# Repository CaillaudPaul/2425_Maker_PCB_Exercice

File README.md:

# 2425_Maker_PCB_Exercice
Creation of a PCB to control a DC motor

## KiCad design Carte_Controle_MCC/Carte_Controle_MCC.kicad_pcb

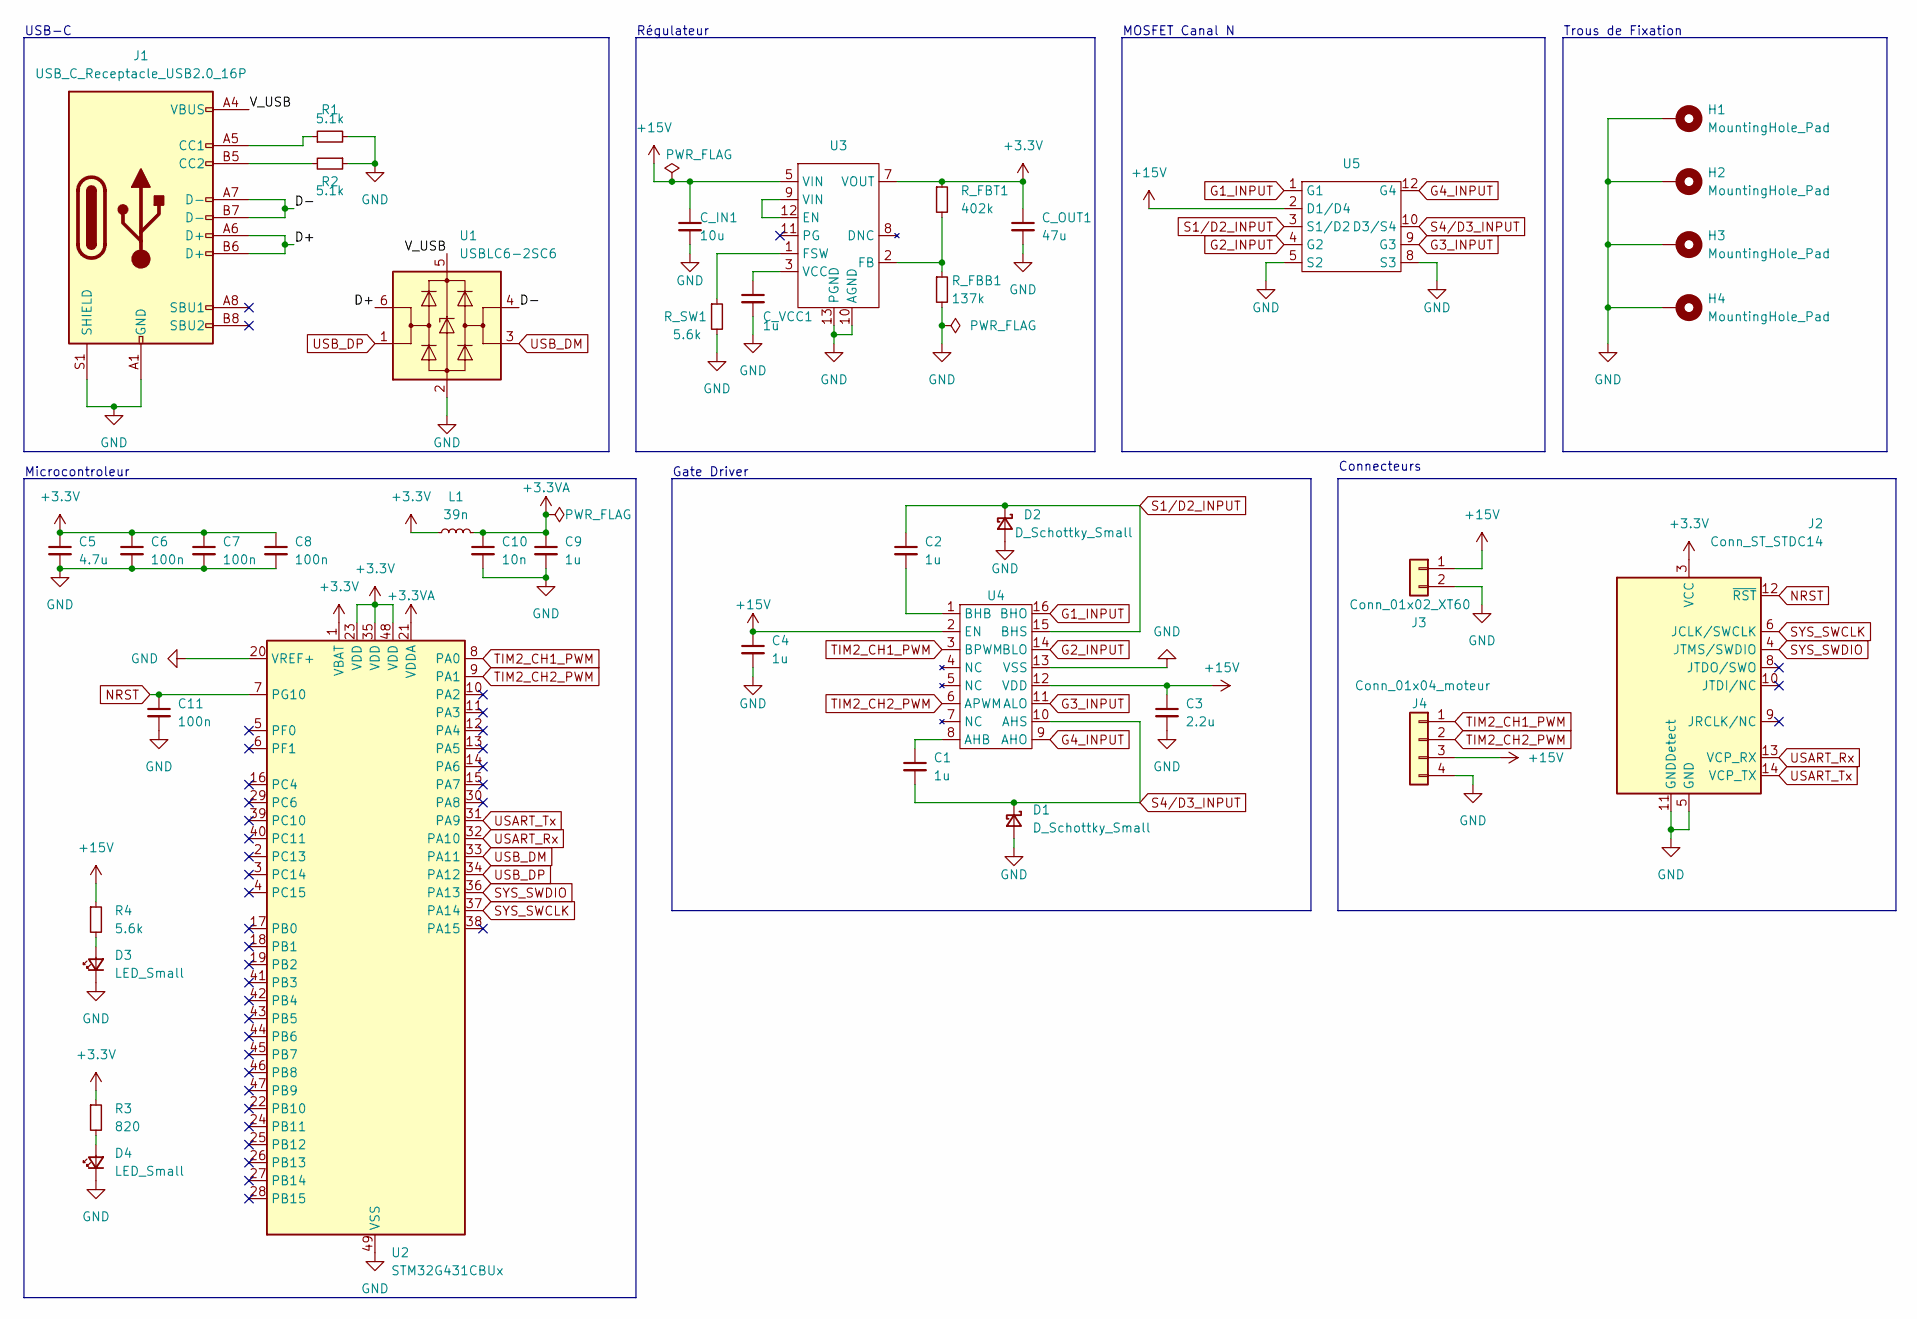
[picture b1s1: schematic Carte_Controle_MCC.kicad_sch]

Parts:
C1, C2, C4, C9: 1u; C_0201_0603Metric_Pad0.64x0.40mm_HandSolder
C3: 2.2u; C_0201_0603Metric_Pad0.64x0.40mm_HandSolder
C5: 4.7u; C_0201_0603Metric_Pad0.64x0.40mm_HandSolder
C6, C7, C8, C11: 100n; C_0201_0603Metric_Pad0.64x0.40mm_HandSolder
C10: 10n; C_0201_0603Metric_Pad0.64x0.40mm_HandSolder
C_IN1: 10u; C_0201_0603Metric_Pad0.64x0.40mm_HandSolder
C_OUT1: 47u; C_0201_0603Metric_Pad0.64x0.40mm_HandSolder
C_VCC1: 1u; C_0201_0603Metric_Pad0.64x0.40mm_HandSolder
D1, D2: D_Schottky_Small; D_0603_1608Metric_Pad1.05x0.95mm_HandSolder
D3, D4: LED_Small; LED_0603_1608Metric_Pad1.05x0.95mm_HandSolder
H1, H2, H3, H4: MountingHole_Pad; MountingHole_3.2mm_M3_DIN965_Pad
J1: USB_C_Receptacle_USB2.0_16P; USB_C_Receptacle_G-Switch_GT-USB-7010ASV
J2: Conn_ST_STDC14; PinHeader_2x07_P1.27mm_Vertical_SMD
J3: Conn_01x02_XT60; AMASS_XT60-M_1x02_P7.20mm_Vertical
J4: Conn_01x04_moteur; JST_EH_B4B-EH-A_1x04_P2.50mm_Vertical
L1: 39n; L_0805_2012Metric_Pad1.05x1.20mm_HandSolder
R1, R2: 5.1k; R_0603_1608Metric_Pad0.98x0.95mm_HandSolder
R3: 820; R_0603_1608Metric_Pad0.98x0.95mm_HandSolder
R4: 5.6k; R_0603_1608Metric_Pad0.98x0.95mm_HandSolder
R_FBB1: 137k; R_0603_1608Metric_Pad0.98x0.95mm_HandSolder
R_FBT1: 402k; R_0603_1608Metric_Pad0.98x0.95mm_HandSolder
R_SW1: 5.6k; R_0603_1608Metric_Pad0.98x0.95mm_HandSolder
U1: USBLC6-2SC6; SOT-23-6
U2: STM32G431CBUx; QFN-48-1EP_7x7mm_P0.5mm_EP5.6x5.6mm
U3: wurth_171013801
U4: Gate_Driver_MIC4606-2YTS-TR
U5: Mosfet_FDMQ86530L

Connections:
+3.3V: C5.1, C6.1, C7.1, C8.1, C_OUT1.1, J2.3 (VCC), L1.1, R3.1, R_FBT1.1, U2.1 (VBAT), U2.23 (VDD), U2.35 (VDD), U2.48 (VDD), U3.6 (VOUT), U3.7 (VOUT)
+3.3VA: C9.1, C10.1, L1.2, U2.21 (VDDA)
+15V: C3.1, C4.1, C_IN1.1, J3.1, J4.3, R4.1, U3.4 (VIN), U3.5 (VIN), U4.2 (EN), U4.12 (VDD), U5.2 (D1/D4), U5.11 (D1/D4), U5.13 (D1/D4)
/D+: J1.A6 (D+), J1.B6 (D+), U1.6 (I/O1)
/D-: J1.A7 (D-), J1.B7 (D-), U1.4 (I/O2)
/V_USB: J1.A4 (VBUS), J1.A9 (VBUS), J1.B4 (VBUS), J1.B9 (VBUS), U1.5 (VBUS)
G1_INPUT: U4.16 (BHO), U5.1 (G1)
G2_INPUT: U4.14 (BLO), U5.4 (G2)
G3_INPUT: U4.11 (ALO), U5.9 (G3)
G4_INPUT: U4.9 (AHO), U5.12 (G4)
GND: C3.2, C4.2, C5.2, C6.2, C7.2, C8.2, C9.2, C10.2, C11.2, C_IN1.2, C_OUT1.2, C_VCC1.2, D1.2 (A), D2.2 (A), D3.1 (K), D4.1 (K), H1.1, H2.1, H3.1, H4.1, J1.A1 (GND), J1.A12 (GND), J1.B1 (GND), J1.B12 (GND), J1.S1 (SHIELD), J2.5 (GND), J2.7 (GND), J2.11 (GNDDetect), J3.2, J4.4, R1.2, R2.1, R_FBB1.2, R_SW1.2, U1.2 (GND), U2.20 (VREF+), U2.49 (VSS), U3.10 (AGND), U3.13 (PGND), U4.13 (VSS), U5.5 (S2), U5.6 (S2), U5.7 (S3), U5.8 (S3)
NRST: C11.1, J2.12 (~RST), U2.7 (PG10)
unnamed: D3.2 (A), R4.2
unnamed: D4.2 (A), R3.2
unnamed: J1.A5 (CC1), R1.1
unnamed: J1.B5 (CC2), R2.2
unnamed: U3.9 (VIN), U3.12 (EN)
unnamed: R_FBB1.1, R_FBT1.2, U3.2 (FB)
unnamed: R_SW1.1, U3.1 (FSW)
unnamed: C_VCC1.1, U3.3 (VCC)
unnamed: C1.1, U4.8 (AHB)
unnamed: C2.2, U4.1 (BHB)
S1/D2_INPUT: C2.1, D2.1 (K), U4.15 (BHS), U5.3 (S1/D2), U5.14 (S1/D2)
S4/D3_INPUT: C1.2, D1.1 (K), U4.10 (AHS), U5.10 (D3/S4), U5.15 (D3/S4)
SYS_SWCLK: J2.6 (JCLK/SWCLK), U2.37 (PA14)
SYS_SWDIO: J2.4 (JTMS/SWDIO), U2.36 (PA13)
TIM2_CH1_PWM: J4.1, U2.8 (PA0), U4.3 (BPWM)
TIM2_CH2_PWM: J4.2, U2.9 (PA1), U4.6 (APWM)
USART_Rx: J2.13 (VCP_RX), U2.32 (PA10)
USART_Tx: J2.14 (VCP_TX), U2.31 (PA9)
USB_DM: U1.3 (I/O2), U2.33 (PA11)
USB_DP: U1.1 (I/O1), U2.34 (PA12)

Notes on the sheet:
Régulateur
MOSFET Canal N
Microcontroleur
Trous de Fixation
Gate Driver
Connecteurs
USB-C

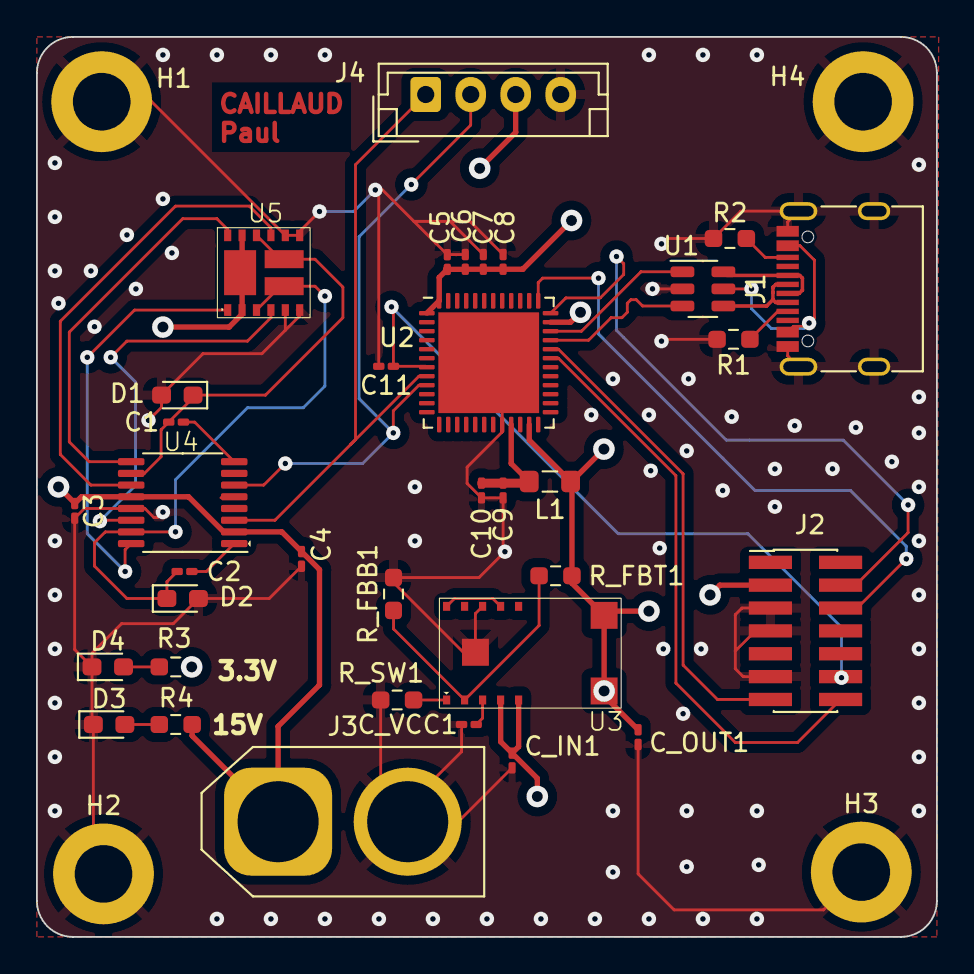
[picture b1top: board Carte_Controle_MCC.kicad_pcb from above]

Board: 4 copper layers, 50.0 x 50.0 mm, 39 parts (0 on the bottom side), 32 nets.

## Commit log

2025-01-30 First schematic commit
2025-01-30 Adding the symbols created
2025-01-31 Update 2
    Correction of the schematic,
    creation of new footprints,
    Association of the footprints and the symbols
2025-02-01 routing of the PCB
2025-02-03 Suppression of unecessary ground tracks
2025-03-19 small_changes
    Small changes on the board
